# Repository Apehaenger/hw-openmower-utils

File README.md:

# OpenMower Hardware Utils

## V2 Mainboard Compatible

### SATA- Breakout Board for V2 Hardware

<a href="./hw-openmower-utils-satabob/">

Pico Breakout Board connected via OpenMower's specific SATA plug</a>
<br clear="left"/>

## V1 Mainboard Compatible

### LSM6DSx IMU for V1 Hardware

<a href="./hw-openmower-utils-v1-j20-lsm6dsx/">

LSM6DSx IMU alternative for J20 @ OpenMower V1 (instead of MPU9250 or WT901)</a>
<br clear="left"/>

### Arduino/UM9x Shield for V1 Hardware

<a href="./hw-openmower-utils-v1-arduino-uno-um9x/">

Simple UM9x GNSS module mount shield for OpenMower V1</a>
<br clear="left"/>

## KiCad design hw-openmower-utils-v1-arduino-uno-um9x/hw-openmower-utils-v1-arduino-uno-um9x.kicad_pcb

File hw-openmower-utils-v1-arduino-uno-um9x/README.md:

# Arduino Uno - UM9x shield for OpenMower V1 Mainboard

## Installation

### Hardware

In the images above, I used 90° pin headers, but you may also use straight ones, in which case the height will be approx. 5mm higher.

As SMA-fastener I used a simple cable straps, but you can also solder a simple looped- wire and fasten it then there.

### Software

If plugged into OpenMower V1 Mainboard, the UM9x will be available at Raspberry Pi's /dev/ttyAMA1 (like the normal GPS module) and use COM2 of UM9x.

I do configure my UM9x with the following 2 steps:

1. Connect to new UM9x with default baud rate and change to higher baud rate via:<br>
   `miniterm /dev/ttyAMA1 115200 -e` and enter:<br>
   FRESET<kbd>⏎ Enter</kbd><br>
   CONFIG COM2 460800<kbd>⏎ Enter</kbd><br>
   Now exit miniterm via <kbd>Ctrl</kbd> + <kbd>]</kbd><br>

1. Connect again to UM9x but with new/higher baud rate via:<br>
   `miniterm /dev/ttyAMA1 460800 -e` and configure GNSS i.e. via:<br>
   MODE ROVER UAV<kbd>⏎ Enter</kbd><br>
   GPGSV COM2 2<kbd>⏎ Enter</kbd><br>
   GPRMC COM2 1<kbd>⏎ Enter</kbd><br>
   GPGSA COM2 1<kbd>⏎ Enter</kbd><br>
   GPVTG COM2 1<kbd>⏎ Enter</kbd><br>
   GPGGA COM2 0.5<kbd>⏎ Enter</kbd><br>
   SAVECONFIG<kbd>⏎ Enter</kbd><br>
   Exit miniterm via <kbd>Ctrl</kbd> + <kbd>]</kbd><br>

Lastly, you need to adapt your mower_config. Change or add the following two lines:<br>

```
export OM_GPS_PROTOCOL=NMEA
export OM_GPS_BAUDRATE=460800
```

## Availability / Production

Pretty cheap to produce (except shipping). Nothing special.

If interested (and resident in EU), I've probably some spares left (for some €). Contact me @Apehaenger in [Discord](https://discord.gg/jE7QNaSxW7)

<p align="right">(<a href="#readme-top">back to top</a>)</p>

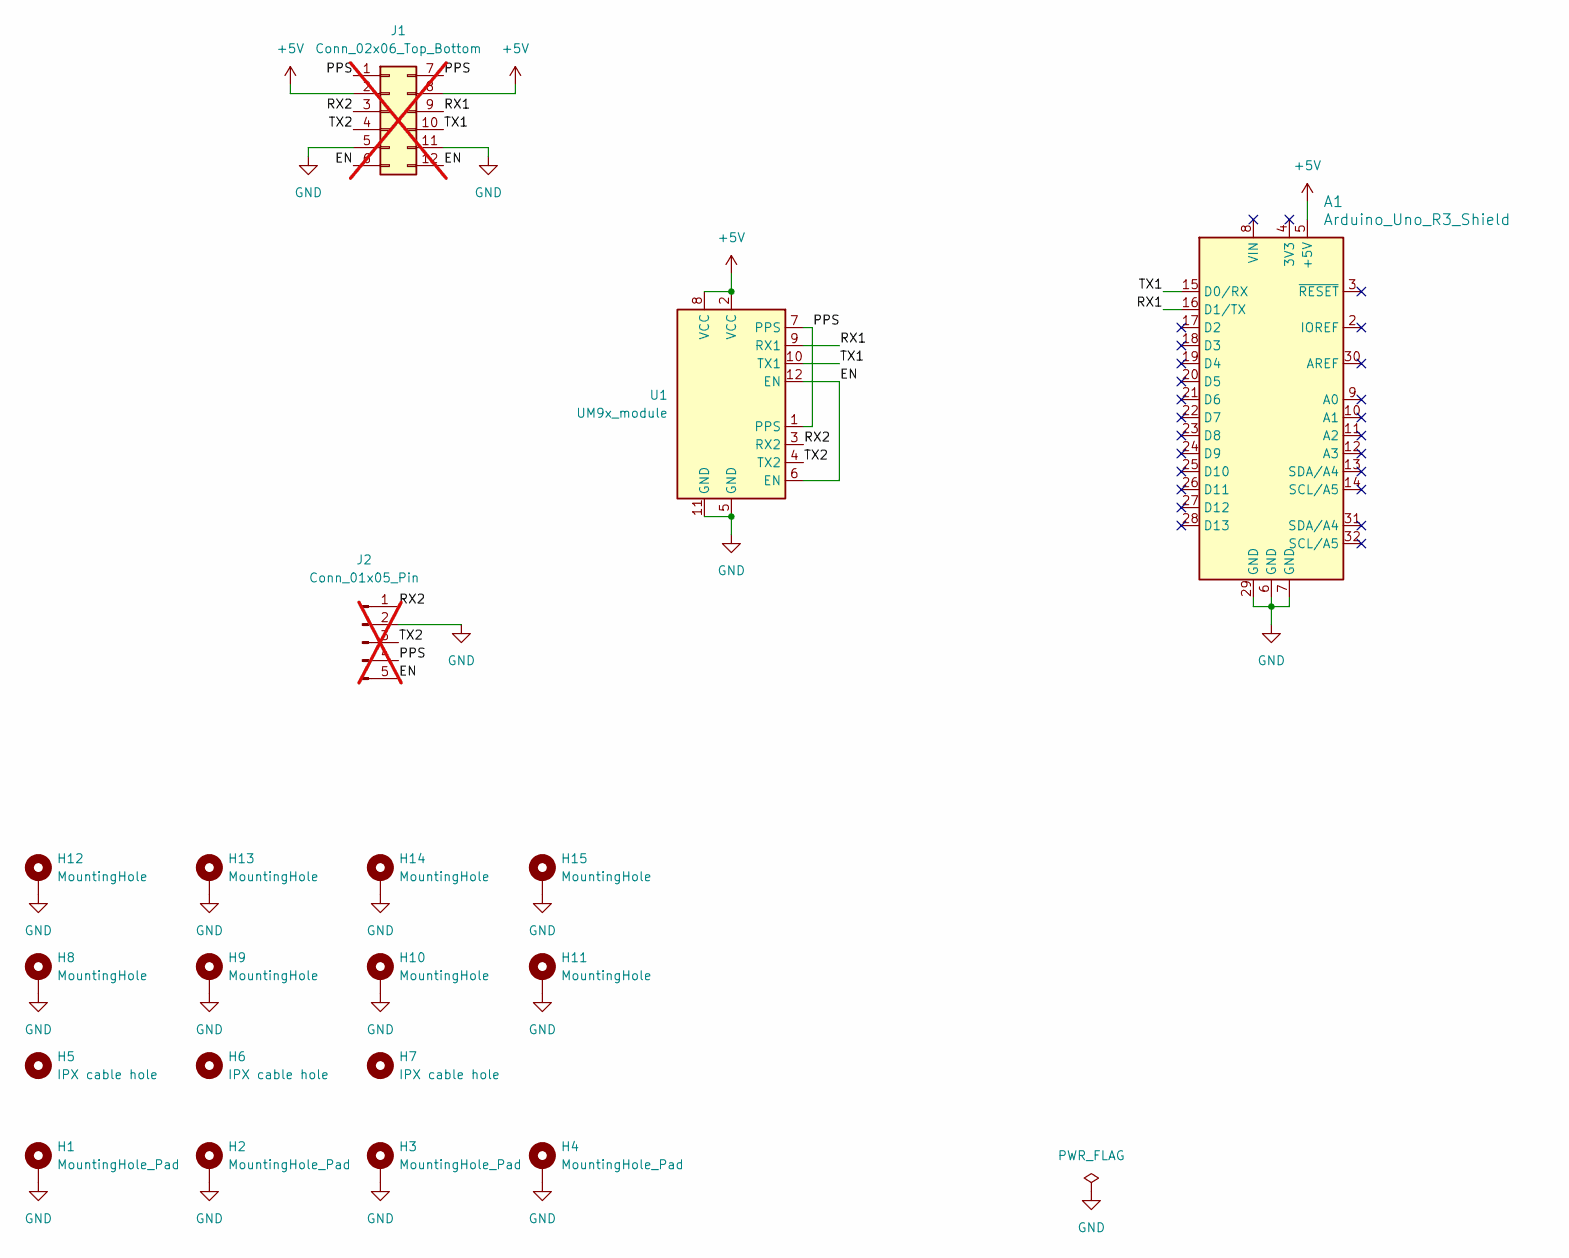
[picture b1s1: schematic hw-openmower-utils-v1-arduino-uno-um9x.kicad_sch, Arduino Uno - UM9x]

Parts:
A1: Arduino_Uno_R3_Shield; Arduino_Uno_R3_OpenMower_Shield
H1, H2, H3, H4: MountingHole_Pad; MountingHole_3.2mm_M3_DIN965_Pad_TopBottom
H5, H6, H7: IPX cable hole; MountingHole_3.2mm_M3
H8, H9, H10, H11, H12, H13, H14, H15: MountingHole; TestPoint_THTPad_D2.0mm_Drill1.0mm
J1: Conn_02x06_Top_Bottom; PinSocket_2x06_P2.54mm_Horizontal_Top_Bottom; not fitted
J2: Conn_01x05_Pin; PinHeader_1x05_P2.54mm_Vertical; not fitted
U1: UM9x_module

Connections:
+5V: A1.5 (+5V), J1.2, J1.8, U1.2 (VCC), U1.8 (VCC)
/EN: J1.6, J1.12, J2.5, U1.6 (EN), U1.12 (EN)
/PPS: J1.1, J1.7, J2.4, U1.1 (PPS), U1.7 (PPS)
/RX1: A1.16 (D1/TX), J1.9, U1.9 (RX1)
/RX2: J1.3, J2.1, U1.3 (RX2)
/TX1: A1.15 (D0/RX), J1.10, U1.10 (TX1)
/TX2: J1.4, J2.3, U1.4 (TX2)
GND: A1.6 (GND), A1.7 (GND), A1.29 (GND), H1.1, H2.1, H3.1, H4.1, H8.1, H9.1, H10.1, H11.1, H12.1, H13.1, H14.1, H15.1, J1.5, J1.11, J2.2, U1.5 (GND), U1.11 (GND)

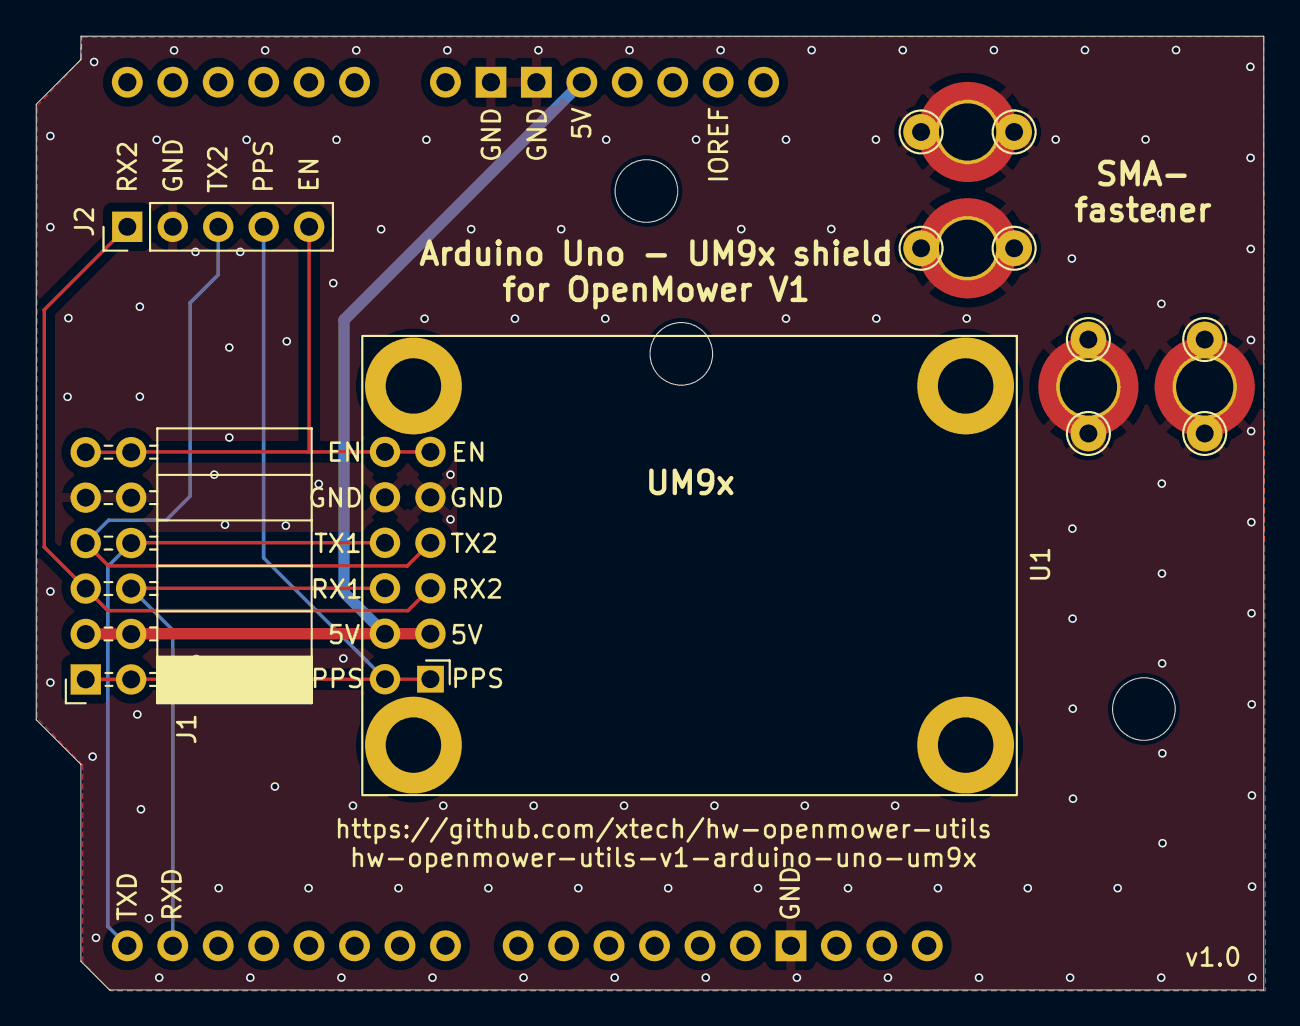
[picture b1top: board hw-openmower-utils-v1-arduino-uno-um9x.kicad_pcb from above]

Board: 2 copper layers, 68.6 x 53.3 mm, 19 parts (0 on the bottom side), 8 nets.

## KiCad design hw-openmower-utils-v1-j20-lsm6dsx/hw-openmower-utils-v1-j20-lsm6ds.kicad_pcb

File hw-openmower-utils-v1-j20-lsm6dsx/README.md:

# LSM6DSx IMU for J20 @ V1 Mainboard

## Motivation

OpenMower V1 Mainboard 0.9.x up to 0.10.x requires an external plugged in IMU into J20.<br>
Unfortunately you don't get a non-faked MPU9250 anymore, so the only alternative you had, is the (non-cheap) WT901 for which you also need to solder an adapter (if you don't wanna block your sound option).

That's why I designed this alternative.

## Compatibility

I used and tested this only on an OpenMower (V1) 0.9.x Mainboard, but it should be compatible also for 0.9.x up to 0.13.x Mainboard variants.
So you should be also able to use it for the case that you've a damaged or malfunction mainboard-assembled IMU (if you disable/remove the assembled one before).

## Installation

Plug into J20 (take attention to Pin-1 direction) and install Firmware with "_LSM6DSO" suffix (for 0.9.x up to 0.11.x). As of 0.12.x LSM6DSO is compiled in by default.

## Availability / Production

Due to the LGA package of LSM6DSx, PCBA production is relatively expensive in special for lower number of pieces (<20).

Please contact me at `joerg` at `ebeling` dot `ws`, I've probably some tested prototypes with an assembled LSM6DSO left for sell.<br>
If you're good in Hot-Plate soldering, I also have some prototypes without assembled LSM6DSO...

<p align="right">(<a href="#readme-top">back to top</a>)</p>

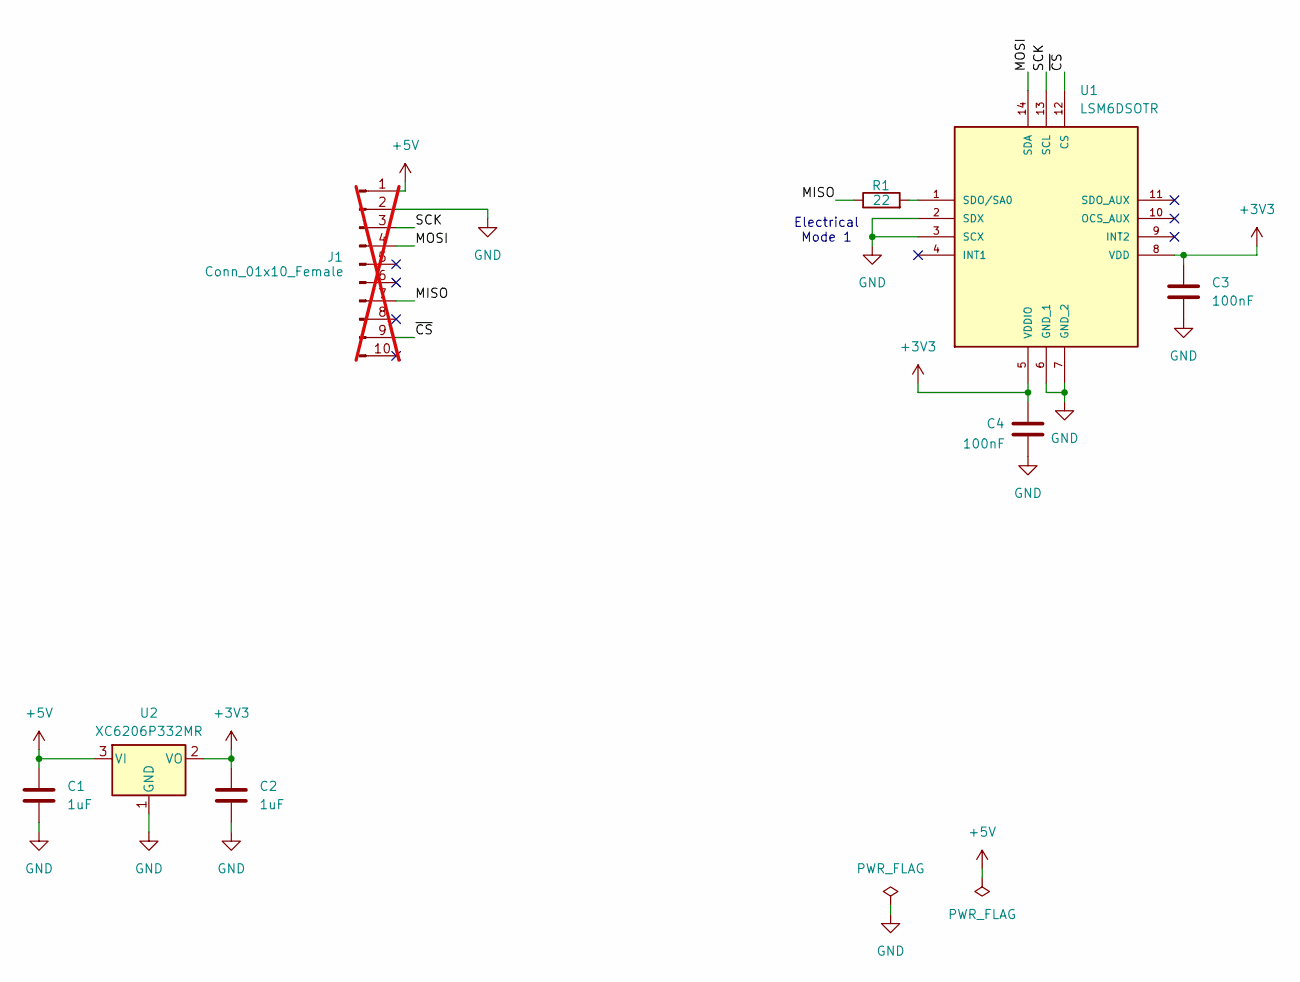
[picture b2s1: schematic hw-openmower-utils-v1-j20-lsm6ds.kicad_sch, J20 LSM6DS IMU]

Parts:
C1, C2: 1uF; C_0603_1608Metric; LCSC C15849
C3, C4: 100nF; C_0603_1608Metric; LCSC C14663
J1: Conn_01x10_Female; PinHeader_1x10_P2.54mm_Vertical; Part Number PZ254-1-10-Z-8.5; LCSC C2894933; not fitted
R1: 22; R_0603_1608Metric; LCSC C23345
U1: LSM6DSOTR; LCSC C2655100
U2: XC6206P332MR; SOT-23-3; LCSC C347376

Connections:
+3V3: C2.1, C3.1, C4.1, U1.5 (VDDIO), U1.8 (VDD), U2.2 (VO)
+5V: C1.1, J1.1, U2.3 (VI)
/MISO: J1.7, R1.1
/MOSI: J1.4, U1.14 (SDA)
/SCK: J1.3, U1.13 (SCL)
/~CS: J1.9, U1.12 (CS)
GND: C1.2, C2.2, C3.2, C4.2, J1.2, U1.2 (SDX), U1.3 (SCX), U1.6 (GND_1), U1.7 (GND_2), U2.1 (GND)
unnamed: R1.2, U1.1 (SDO/SA0)

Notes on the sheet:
Electrical Mode 1

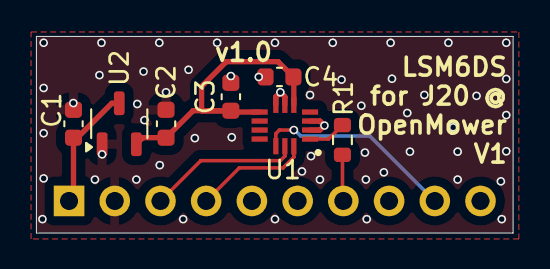
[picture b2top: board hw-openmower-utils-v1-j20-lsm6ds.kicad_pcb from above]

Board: 2 copper layers, 26.5 x 10.9 mm, 8 parts (1 on the bottom side), 8 nets.

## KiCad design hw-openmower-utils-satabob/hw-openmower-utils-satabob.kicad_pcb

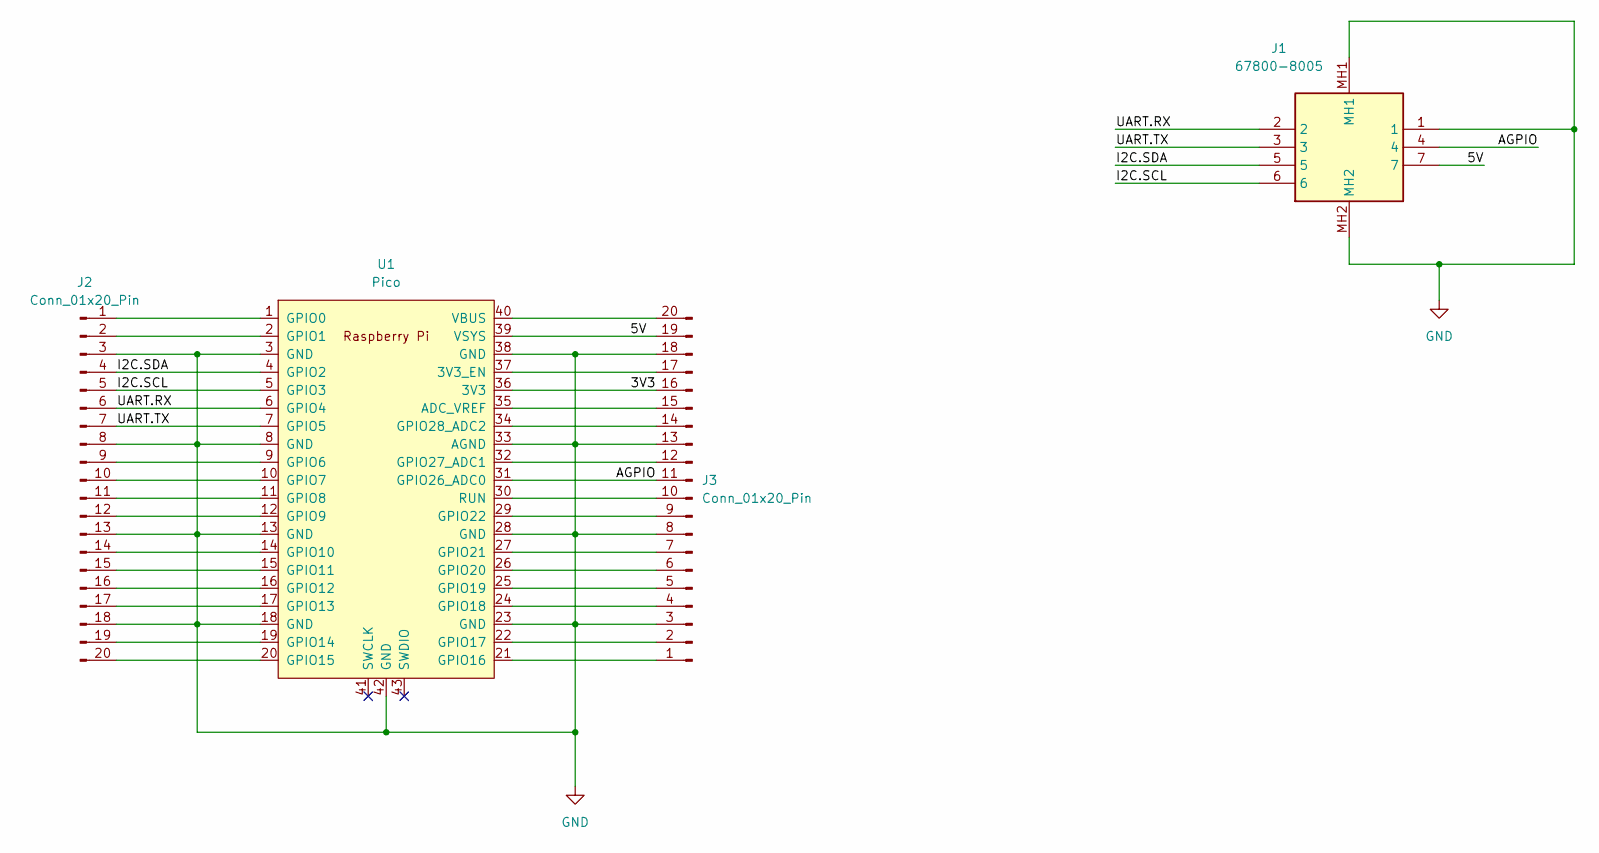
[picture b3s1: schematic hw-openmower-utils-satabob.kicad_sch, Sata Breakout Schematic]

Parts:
J1: 67800-8005; SATA-Molex-67800-8005; Mouser Part Number 538-67800-8005
J2, J3: Conn_01x20_Pin; PinHeader_1x20_P2.54mm_Vertical
U1: Pico; RPi_Pico_SMD_TH

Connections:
/3V3: J3.16, U1.36 (3V3)
/5V: J1.7, J3.19, U1.39 (VSYS)
/AGPIO: J1.4, J3.11, U1.31 (GPIO26_ADC0)
/I2C.SCL: J1.6, J2.5, U1.5 (GPIO3)
/I2C.SDA: J1.5, J2.4, U1.4 (GPIO2)
/UART.RX: J1.2, J2.6, U1.6 (GPIO4)
/UART.TX: J1.3, J2.7, U1.7 (GPIO5)
GND: J1.1, J1.MH1, J1.MH2, J2.3, J2.8, J2.13, J2.18, J3.3, J3.8, J3.13, J3.18, U1.3 (GND), U1.8 (GND), U1.13 (GND), U1.18 (GND), U1.23 (GND), U1.28 (GND), U1.33 (AGND), U1.38 (GND), U1.42 (GND)
unnamed: J2.1, U1.1 (GPIO0)
unnamed: J2.2, U1.2 (GPIO1)
unnamed: J2.9, U1.9 (GPIO6)
unnamed: J2.10, U1.10 (GPIO7)
unnamed: J2.11, U1.11 (GPIO8)
unnamed: J2.12, U1.12 (GPIO9)
unnamed: J2.14, U1.14 (GPIO10)
unnamed: J2.15, U1.15 (GPIO11)
unnamed: J2.16, U1.16 (GPIO12)
unnamed: J2.17, U1.17 (GPIO13)
unnamed: J2.19, U1.19 (GPIO14)
unnamed: J2.20, U1.20 (GPIO15)
unnamed: J3.1, U1.21 (GPIO16)
unnamed: J3.2, U1.22 (GPIO17)
unnamed: J3.4, U1.24 (GPIO18)
unnamed: J3.5, U1.25 (GPIO19)
unnamed: J3.6, U1.26 (GPIO20)
unnamed: J3.7, U1.27 (GPIO21)
unnamed: J3.9, U1.29 (GPIO22)
unnamed: J3.10, U1.30 (RUN)
unnamed: J3.12, U1.32 (GPIO27_ADC1)
unnamed: J3.14, U1.34 (GPIO28_ADC2)
unnamed: J3.15, U1.35 (ADC_VREF)
unnamed: J3.17, U1.37 (3V3_EN)
unnamed: J3.20, U1.40 (VBUS)

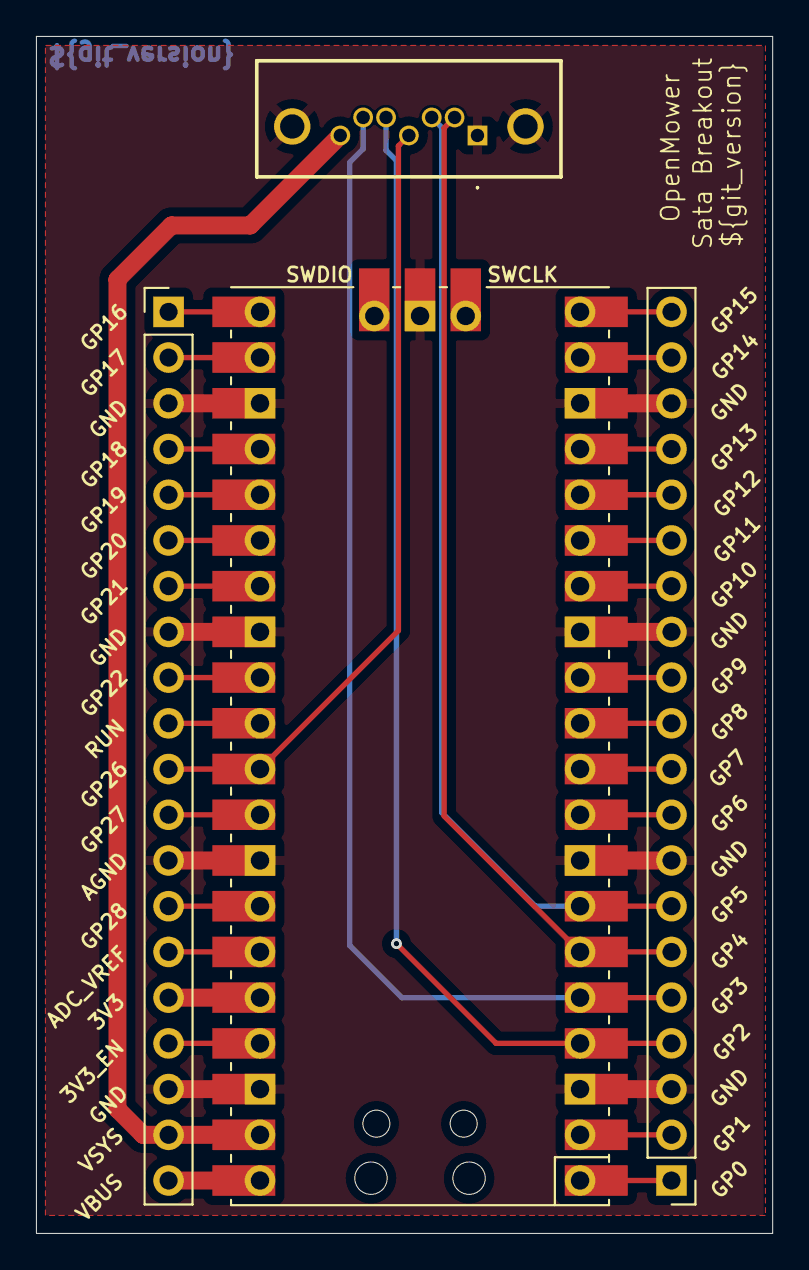
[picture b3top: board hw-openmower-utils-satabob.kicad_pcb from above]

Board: 2 copper layers, 40.9 x 66.5 mm, 4 parts (0 on the bottom side), 33 nets.

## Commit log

2024-10-21 Initial commit of sata breakout files
2024-10-21 Uploading components files
2024-10-21 Added gitignore, missing libs and cleaned mac crap
2024-10-21 added CI
2024-10-21 added gitignore
2024-10-21 added git version to pcb
2024-10-21 wip CI
2025-01-09 LSM6DSx & docs
2025-01-20 Arduino-Uno-UM9x-Shield

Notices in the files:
hw-openmower-utils-v1-arduino-uno-um9x/hw-openmower-utils-v1-arduino-uno-um9x.kicad_pcb:
Creative Commons Attribution-NonCommercial-ShareAlike 4.0 International License.
Licensed under
